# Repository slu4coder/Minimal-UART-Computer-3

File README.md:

# Minimal UART Computer 3 - Blinkenlights!

Here comes a big update of my DIY 'Minimal UART Computer', a machine built around a serial interface just from a handful of logic ICs, RAM and FLASH memory. For it's size, simplicity and self-imposed limitations, it's got double the processing power of a Commodore C64 or Apple II. It's mission is to be a fun learning platform for understanding computers on a fundamental level.

This is a free and non-commercial project. I am in no way associated with any activies selling the 'Minimal UART Computer' as a product. Any such activity represents a license violation. Individual licenses apply for hardware and software parts. Please refer to the applicable documentations for detailed licensing information. 

● Manual: https://docs.google.com/document/d/1nIM-WRrVe7SzYY-DS1jcVHC4TCuIhlQ6LCHnZnEml7k/edit?usp=sharing

● The Minimal UART Computer has a dedicated hardware serial 'Minimal Terminal': https://github.com/slu4coder/Minimal-Terminal
but can also be operated via a USB-to-serial breakout board and a terminal emulation (e. g. Tera Term) of cause.
  
OVERVIEW:

● Textbook 'Von-Neumann' architecture, 8-bit data bus, 16-bit address bus

● 64 instructions (conditional branching, subroutines, stack and word operations)

● 32KB RAM, 32KB SSD with file system (format, load, save, dir, delete, defrag, ...)

● Adjustable UART I/O (7 data bits, 2 stop bits, 9600bps – 500000bps)

● Adjustable CPU clock speed (single step – 8MHz)

● Processing power ~1.1Mips @ 8MHz comparable to 2x Commodore 64 or 2x Apple II

● Clear(est?) and simple(st? – you judge!) design

● ALU with 2 data registers A & B

● 3 flags (zero, negative, carry)

● 24 control signals

● Only 30(!) 74HCxx logic ICs, RAM and FLASH (an ATmega328p is used as a variable clock generator)

● NEW: Blinkenlights ;-)

● Operating system wiht native assembler and editor

● Games and demos (Tetris, Mandelbrot)

● Cycle-exact emulator, cross-assembler (Win64 and Linux)

I hope you find this information useful, educational or otherwise interesting. I'd love to hear about your build, so meet me on YouTube:

https://www.youtube.com/watch?v=wpls_rTcvJ8

https://www.youtube.com/channel/UCXYQcMpUBT3aaQKfmAVJNow

This is a free and non-commercial project. I am in no way associated with any activies selling this as a product.
Any such activity represents a license violation. Individual licenses apply for hardware and software parts. Please refer to the
appropriate documentations for detailed licensing information.

See https://github.com/slu4coder/Minimal-64x4-Home-Computer for a more feature-rich alternative with bitmap graphics, VGA and PS/2.

If you like this project and want to give something back, you can do so via PayPal. Thanks!

https://paypal.me/CarstenHerting

Have fun!

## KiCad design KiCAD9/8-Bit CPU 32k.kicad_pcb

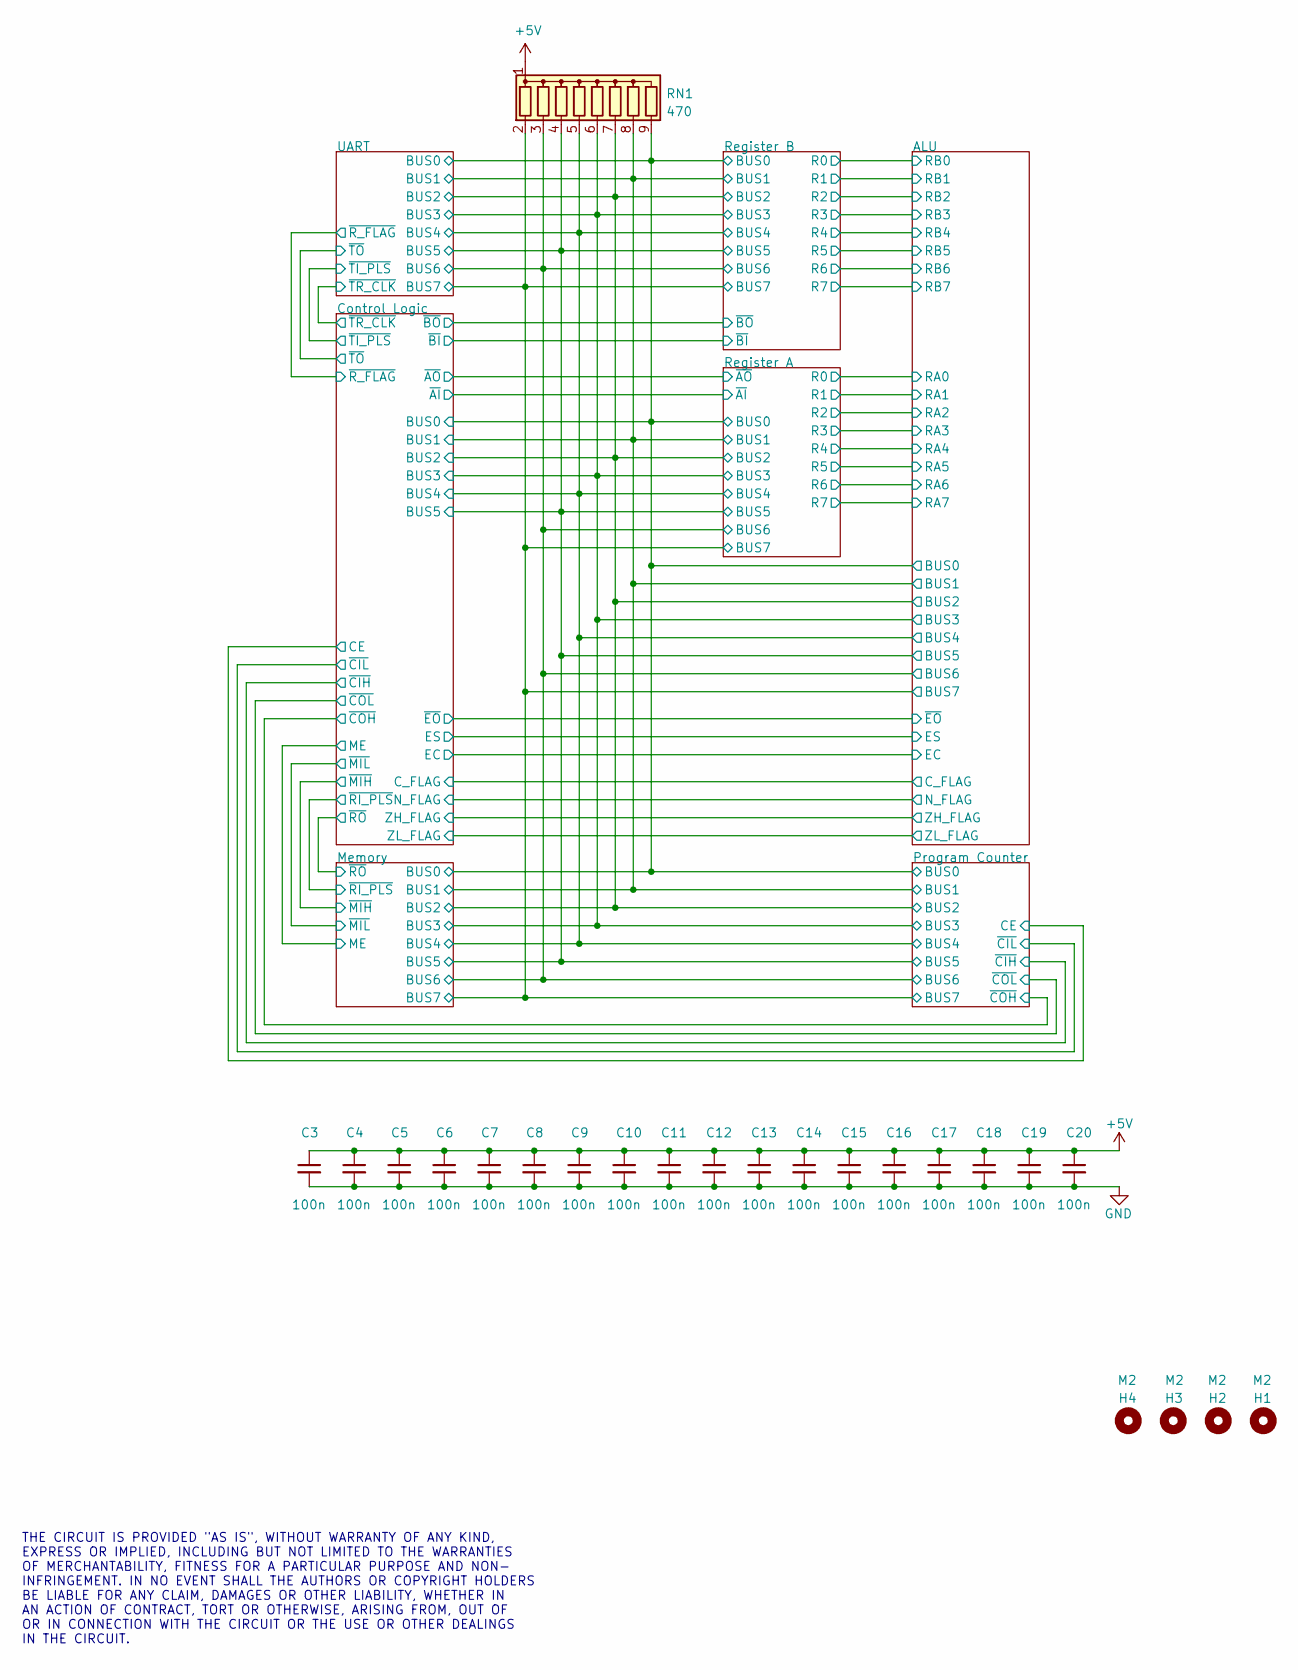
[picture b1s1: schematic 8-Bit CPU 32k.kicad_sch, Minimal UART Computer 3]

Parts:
C3, C4, C5, C6, C7, C8, C9, C10, C11, C12, C13, C14, C15, C16, C17, C18, C19, C20: 100n; C_Disc_D3.0mm_W2.0mm_P2.50mm
H1, H2, H3, H4: M2; MountingHole_2.2mm_M2
RN1: 470; R_Array_SIP9

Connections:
+5V: C3.1, C4.1, C5.1, C6.1, C7.1, C8.1, C9.1, C10.1, C11.1, C12.1, C13.1, C14.1, C15.1, C16.1, C17.1, C18.1, C19.1, C20.1, RN1.1 (common); also elsewhere on the board
/ALU/BUS0: RN1.9 (R8); also elsewhere on the board
/ALU/BUS1: RN1.8 (R7); also elsewhere on the board
/ALU/BUS2: RN1.7 (R6); also elsewhere on the board
/ALU/BUS3: RN1.6 (R5); also elsewhere on the board
/ALU/BUS4: RN1.5 (R4); also elsewhere on the board
/ALU/BUS5: RN1.4 (R3); also elsewhere on the board
/ALU/BUS6: RN1.3 (R2); also elsewhere on the board
/ALU/BUS7: RN1.2 (R1); also elsewhere on the board
GND: C3.2, C4.2, C5.2, C6.2, C7.2, C8.2, C9.2, C10.2, C11.2, C12.2, C13.2, C14.2, C15.2, C16.2, C17.2, C18.2, C19.2, C20.2; also elsewhere on the board

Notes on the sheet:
THE CIRCUIT IS PROVIDED "AS IS", WITHOUT WARRANTY OF ANY KIND, EXPRESS OR IMPLIED, INCLUDING BUT NOT LIMITED TO THE WARRANTIES OF MERCHANTABILITY, FITNESS FOR A PARTICULAR PURPOSE AND NON- INFRINGEMENT. IN NO EVENT SHALL THE AUTHORS OR COPYRIGHT HOLDERS BE LIABLE FOR ANY CLAIM, DAMAGES OR OTHER LIA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

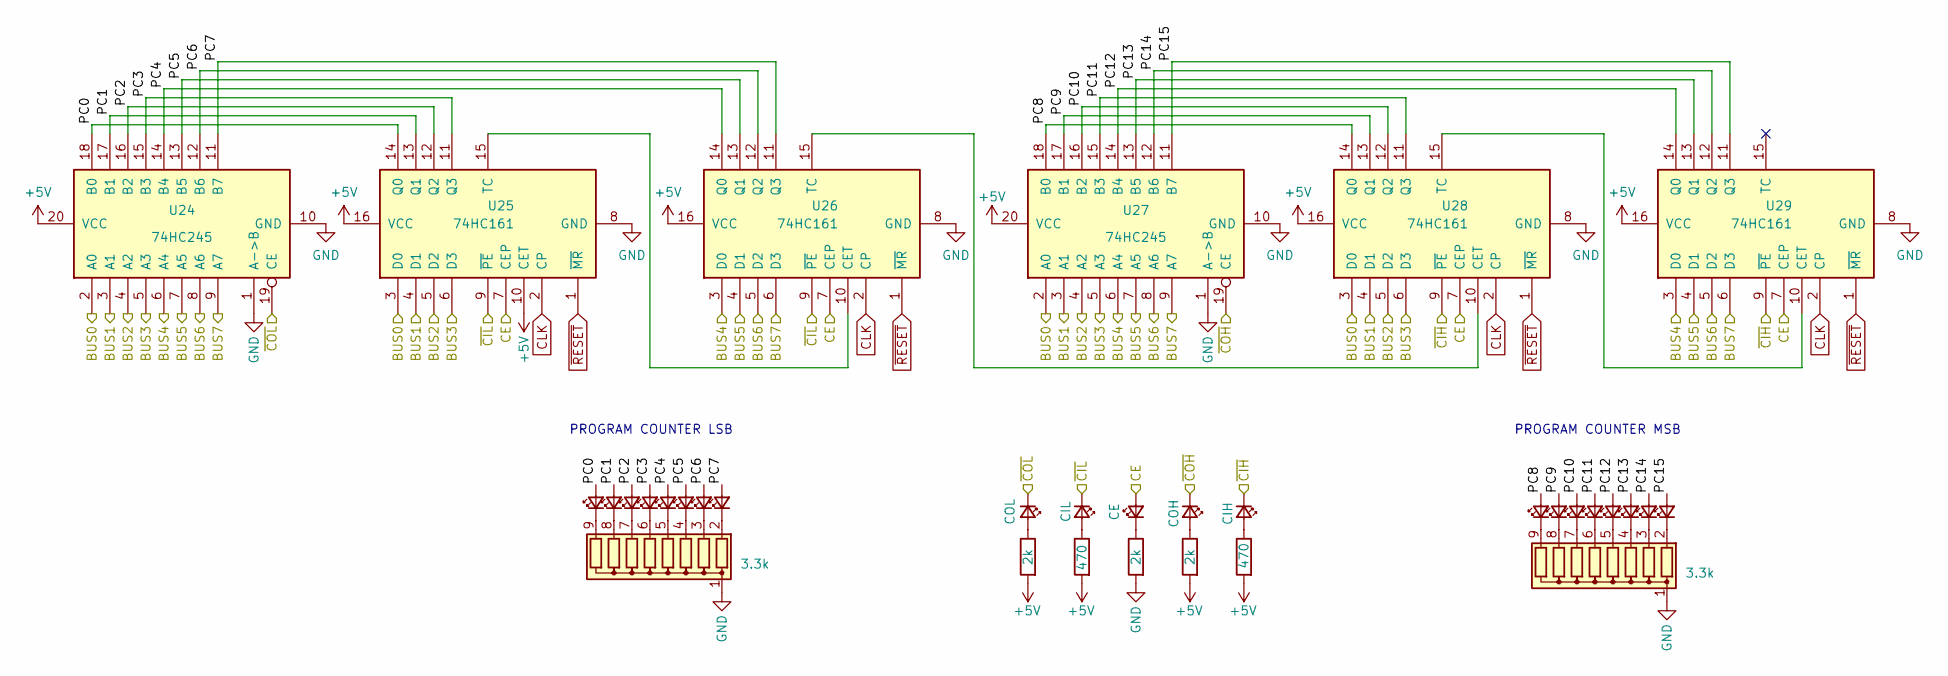
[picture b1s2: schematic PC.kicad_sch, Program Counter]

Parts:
D20, D21, D22, D23, D24, D25, D26, D27, D28, D29, D30, D31, D32, D33, D34, D35: LED_Small; LED_D5.0mm
D79: CIH; LED_D5.0mm
D81: COH; LED_D5.0mm
D83: COL; LED_D5.0mm
D84: CIL; LED_D5.0mm
D92: CE; LED_D5.0mm
R12, R17: 470; R_Axial_DIN0207_L6.3mm_D2.5mm_P7.62mm_Horizontal
R14, R16, R25: 2k; R_Axial_DIN0207_L6.3mm_D2.5mm_P7.62mm_Horizontal
RN4, RN5: 3.3k; R_Array_SIP9
U24, U27: 74HC245; DIP-20_W7.62mm
U25, U26, U28, U29: 74HC161; DIP-16_W7.62mm

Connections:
+5V: R12.2, R14.2, R16.2, R17.2, U24.20 (VCC), U25.10 (CET), U25.16 (VCC), U26.16 (VCC), U27.20 (VCC), U28.16 (VCC), U29.16 (VCC); also elsewhere on the board
/ALU/BUS0: U24.2 (A0), U25.3 (D0), U27.2 (A0), U28.3 (D0); also elsewhere on the board
/ALU/BUS1: U24.3 (A1), U25.4 (D1), U27.3 (A1), U28.4 (D1); also elsewhere on the board
/ALU/BUS2: U24.4 (A2), U25.5 (D2), U27.4 (A2), U28.5 (D2); also elsewhere on the board
/ALU/BUS3: U24.5 (A3), U25.6 (D3), U27.5 (A3), U28.6 (D3); also elsewhere on the board
/ALU/BUS4: U24.6 (A4), U26.3 (D0), U27.6 (A4), U29.3 (D0); also elsewhere on the board
/ALU/BUS5: U24.7 (A5), U26.4 (D1), U27.7 (A5), U29.4 (D1); also elsewhere on the board
/ALU/BUS6: U24.8 (A6), U26.5 (D2), U27.8 (A6), U29.5 (D2); also elsewhere on the board
/ALU/BUS7: U24.9 (A7), U26.6 (D3), U27.9 (A7), U29.6 (D3); also elsewhere on the board
/Control Logic/CE: D92.2 (A), U25.7 (CEP), U26.7 (CEP), U28.7 (CEP), U29.7 (CEP); also elsewhere on the board
/Control Logic/~CIH: D79.1 (K), U28.9 (~PE), U29.9 (~PE); also elsewhere on the board
/Control Logic/~CIL: D84.1 (K), U25.9 (~PE), U26.9 (~PE); also elsewhere on the board
/Control Logic/~COH: D81.1 (K), U27.19 (CE); also elsewhere on the board
/Control Logic/~COL: D83.1 (K), U24.19 (CE); also elsewhere on the board
/Program Counter/PC0: D20.2 (A), U24.18 (B0), U25.14 (Q0)
/Program Counter/PC1: D21.2 (A), U24.17 (B1), U25.13 (Q1)
/Program Counter/PC2: D22.2 (A), U24.16 (B2), U25.12 (Q2)
/Program Counter/PC3: D23.2 (A), U24.15 (B3), U25.11 (Q3)
/Program Counter/PC4: D24.2 (A), U24.14 (B4), U26.14 (Q0)
/Program Counter/PC5: D25.2 (A), U24.13 (B5), U26.13 (Q1)
/Program Counter/PC6: D26.2 (A), U24.12 (B6), U26.12 (Q2)
/Program Counter/PC7: D27.2 (A), U24.11 (B7), U26.11 (Q3)
/Program Counter/PC8: D28.2 (A), U27.18 (B0), U28.14 (Q0)
/Program Counter/PC9: D29.2 (A), U27.17 (B1), U28.13 (Q1)
/Program Counter/PC10: D30.2 (A), U27.16 (B2), U28.12 (Q2)
/Program Counter/PC11: D31.2 (A), U27.15 (B3), U28.11 (Q3)
/Program Counter/PC12: D32.2 (A), U27.14 (B4), U29.14 (Q0)
/Program Counter/PC13: D33.2 (A), U27.13 (B5), U29.13 (Q1)
/Program Counter/PC14: D34.2 (A), U27.12 (B6), U29.12 (Q2)
/Program Counter/PC15: D35.2 (A), U27.11 (B7), U29.11 (Q3)
CLK: U25.2 (CP), U26.2 (CP), U28.2 (CP), U29.2 (CP); also elsewhere on the board
GND: R25.2, RN4.1 (common), RN5.1 (common), U24.1 (A->B), U24.10 (GND), U25.8 (GND), U26.8 (GND), U27.1 (A->B), U27.10 (GND), U28.8 (GND), U29.8 (GND); also elsewhere on the board
unnamed: D20.1 (K), RN4.9 (R8)
unnamed: D21.1 (K), RN4.8 (R7)
unnamed: D22.1 (K), RN4.7 (R6)
unnamed: D23.1 (K), RN4.6 (R5)
unnamed: D24.1 (K), RN4.5 (R4)
unnamed: D25.1 (K), RN4.4 (R3)
unnamed: D26.1 (K), RN4.3 (R2)
unnamed: D27.1 (K), RN4.2 (R1)
unnamed: D28.1 (K), RN5.9 (R8)
unnamed: D29.1 (K), RN5.8 (R7)
unnamed: D30.1 (K), RN5.7 (R6)
unnamed: D31.1 (K), RN5.6 (R5)
unnamed: D32.1 (K), RN5.5 (R4)
unnamed: D33.1 (K), RN5.4 (R3)
unnamed: D34.1 (K), RN5.3 (R2)
unnamed: D35.1 (K), RN5.2 (R1)
unnamed: D79.2 (A), R12.1
unnamed: D81.2 (A), R14.1
unnamed: D83.2 (A), R16.1
unnamed: D84.2 (A), R17.1
unnamed: D92.1 (K), R25.1
unnamed: U25.15 (TC), U26.10 (CET)
unnamed: U26.15 (TC), U28.10 (CET)
unnamed: U28.15 (TC), U29.10 (CET)
~RESET: U25.1 (~MR), U26.1 (~MR), U28.1 (~MR), U29.1 (~MR); also elsewhere on the board

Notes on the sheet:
PROGRAM COUNTER MSB
PROGRAM COUNTER LSB

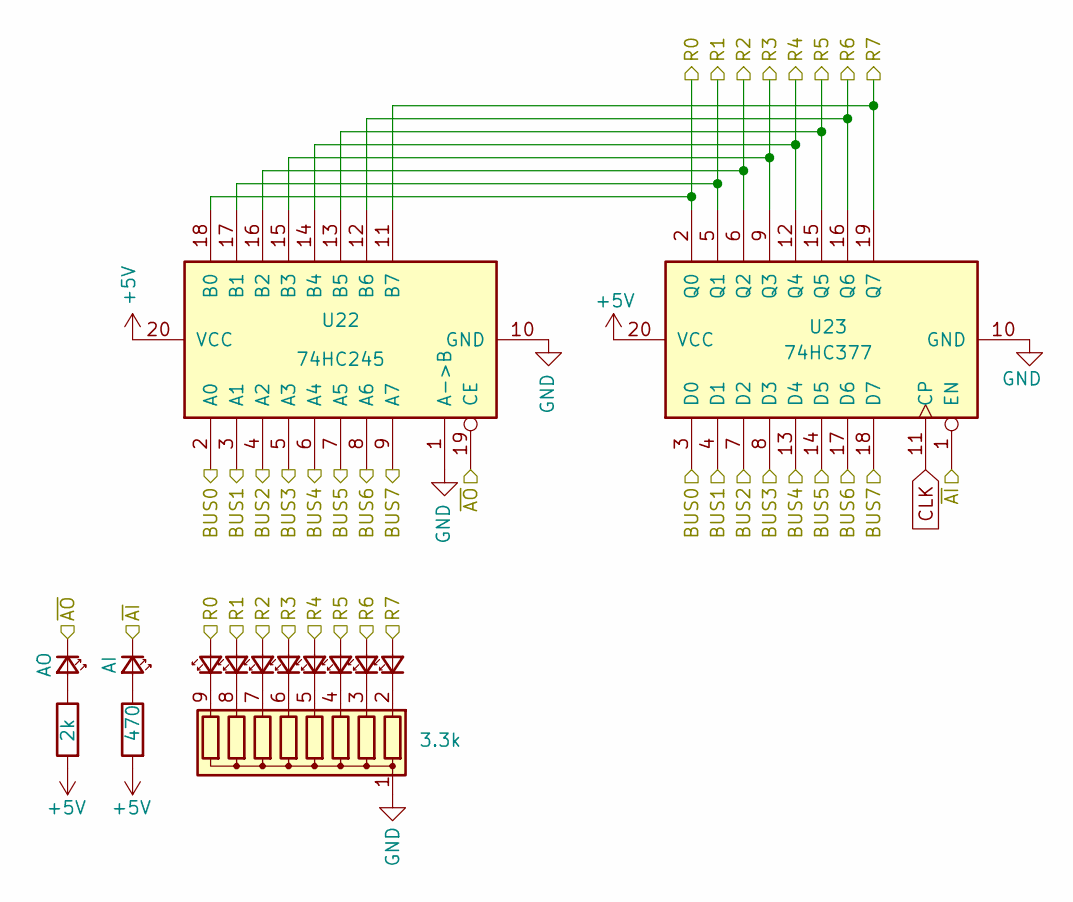
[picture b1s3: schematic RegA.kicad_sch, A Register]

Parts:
D36, D37, D38, D39, D40, D41, D42, D43: LED_Small; LED_D5.0mm
D65: AI; LED_D5.0mm
D66: AO; LED_D5.0mm
R7: 470; R_Axial_DIN0207_L6.3mm_D2.5mm_P7.62mm_Horizontal
R8: 2k; R_Axial_DIN0207_L6.3mm_D2.5mm_P7.62mm_Horizontal
RN6: 3.3k; R_Array_SIP9
U22: 74HC245; DIP-20_W7.62mm
U23: 74HC377; DIP-20_W7.62mm

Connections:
+5V: R7.2, R8.2, U22.20 (VCC), U23.20 (VCC); also elsewhere on the board
/ALU/BUS0: U22.2 (A0), U23.3 (D0); also elsewhere on the board
/ALU/BUS1: U22.3 (A1), U23.4 (D1); also elsewhere on the board
/ALU/BUS2: U22.4 (A2), U23.7 (D2); also elsewhere on the board
/ALU/BUS3: U22.5 (A3), U23.8 (D3); also elsewhere on the board
/ALU/BUS4: U22.6 (A4), U23.13 (D4); also elsewhere on the board
/ALU/BUS5: U22.7 (A5), U23.14 (D5); also elsewhere on the board
/ALU/BUS6: U22.8 (A6), U23.17 (D6); also elsewhere on the board
/ALU/BUS7: U22.9 (A7), U23.18 (D7); also elsewhere on the board
/ALU/RA0: D36.2 (A), U22.18 (B0), U23.2 (Q0); also elsewhere on the board
/ALU/RA1: D37.2 (A), U22.17 (B1), U23.5 (Q1); also elsewhere on the board
/ALU/RA2: D38.2 (A), U22.16 (B2), U23.6 (Q2); also elsewhere on the board
/ALU/RA3: D39.2 (A), U22.15 (B3), U23.9 (Q3); also elsewhere on the board
/ALU/RA4: D40.2 (A), U22.14 (B4), U23.12 (Q4); also elsewhere on the board
/ALU/RA5: D41.2 (A), U22.13 (B5), U23.15 (Q5); also elsewhere on the board
/ALU/RA6: D42.2 (A), U22.12 (B6), U23.16 (Q6); also elsewhere on the board
/ALU/RA7: D43.2 (A), U22.11 (B7), U23.19 (Q7); also elsewhere on the board
/Control Logic/~AI: D65.1 (K), U23.1 (EN); also elsewhere on the board
/Control Logic/~AO: D66.1 (K), U22.19 (CE); also elsewhere on the board
CLK: U23.11 (CP); also elsewhere on the board
GND: RN6.1 (common), U22.1 (A->B), U22.10 (GND), U23.10 (GND); also elsewhere on the board
unnamed: D36.1 (K), RN6.9 (R8)
unnamed: D37.1 (K), RN6.8 (R7)
unnamed: D38.1 (K), RN6.7 (R6)
unnamed: D39.1 (K), RN6.6 (R5)
unnamed: D40.1 (K), RN6.5 (R4)
unnamed: D41.1 (K), RN6.4 (R3)
unnamed: D42.1 (K), RN6.3 (R2)
unnamed: D43.1 (K), RN6.2 (R1)
unnamed: D65.2 (A), R7.1
unnamed: D66.2 (A), R8.1

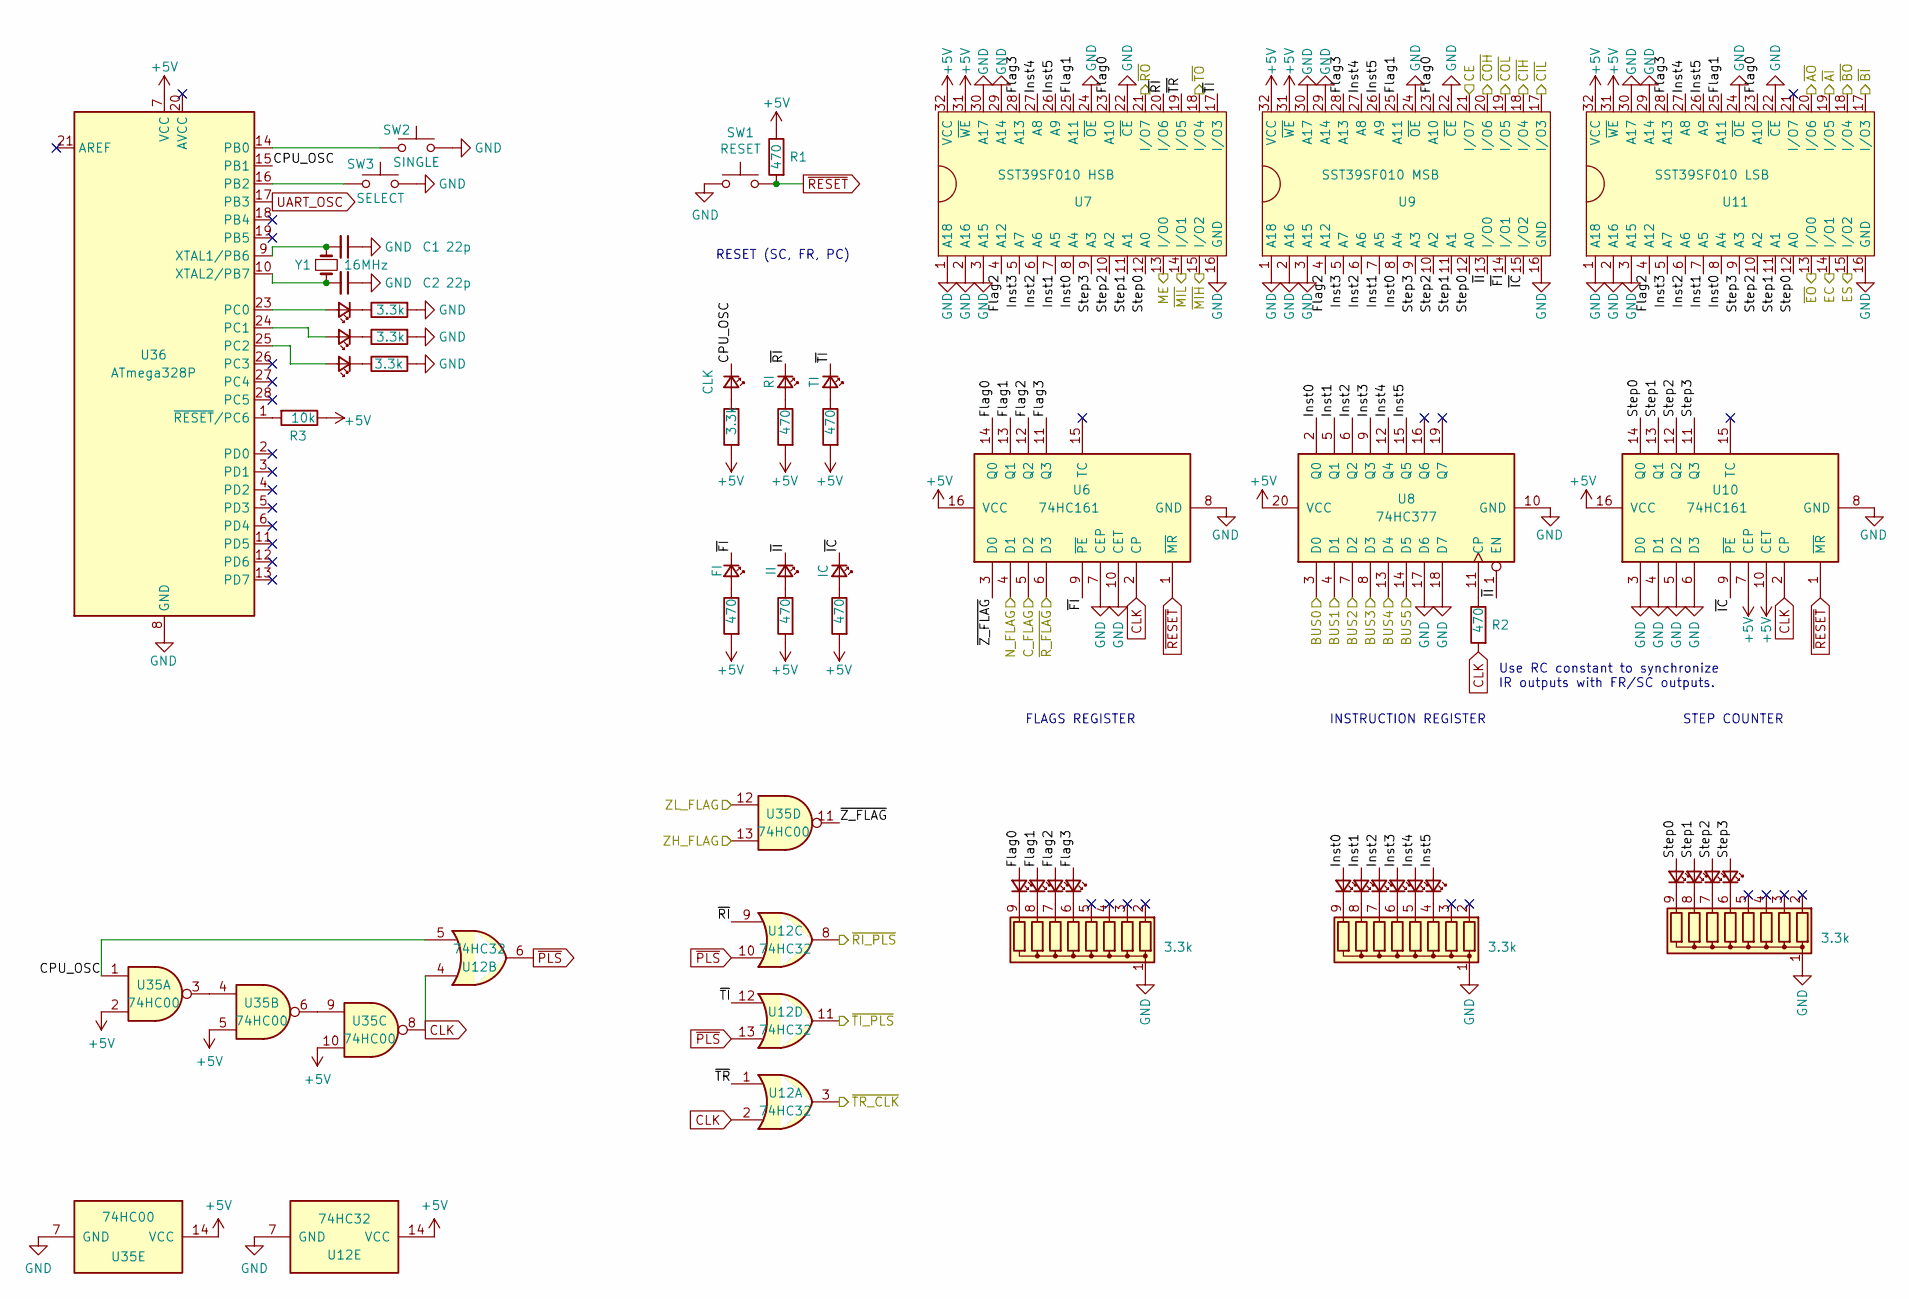
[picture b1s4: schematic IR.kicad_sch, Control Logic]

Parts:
C1, C2: 22p; C_Disc_D5.0mm_W2.5mm_P2.50mm
D1, D2, D3: LED_small; LED_D5.0mm
D60, D61, D62, D63, D64, D67, D68, D69, D70, D71, D72, D73, D74, D75: LED_Small; LED_D5.0mm
D82: RI; LED_D5.0mm
D87: TI; LED_D5.0mm
D89: FI; LED_D5.0mm
D90: II; LED_D5.0mm
D91: IC; LED_D5.0mm
D100: CLK; LED_D5.0mm
R1, R2, R15, R20, R22, R23, R24: 470; R_Axial_DIN0207_L6.3mm_D2.5mm_P7.62mm_Horizontal
R3: 10k; R_Axial_DIN0207_L6.3mm_D2.5mm_P7.62mm_Horizontal
R4, R5, R6, R33: 3.3k; R_Axial_DIN0207_L6.3mm_D2.5mm_P7.62mm_Horizontal
RN9, RN10, RN11: 3.3k; R_Array_SIP9
SW1: RESET; SW_PUSH_6mm
SW2: SINGLE; SW_PUSH_6mm
SW3: SELECT; SW_PUSH_6mm
U6, U10: 74HC161; DIP-16_W7.62mm
U7: SST39SF010 HSB; DIP-32_W15.24mm
U8: 74HC377; DIP-20_W7.62mm
U9: SST39SF010 MSB; DIP-32_W15.24mm
U11: SST39SF010 LSB; DIP-32_W15.24mm
U12: 74HC32; DIP-14_W7.62mm
U35: 74HC00; DIP-14_W7.62mm
U36: ATmega328P; DIP-28_W7.62mm
Y1: 16MHz; Crystal_HC18-U_Vertical

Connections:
+5V: R1.1, R3.1, R15.2, R20.2, R22.2, R23.2, R24.2, R33.2, U6.16 (VCC), U7.31 (~WE), U7.32 (VCC), U8.20 (VCC), U9.31 (~WE), U9.32 (VCC), U10.7 (CEP), U10.10 (CET), U10.16 (VCC), U11.31 (~WE), U11.32 (VCC), U12.14 (VCC), U35.2, U35.5, U35.10, U35.14 (VCC), U36.7 (VCC); also elsewhere on the board
/ALU/BUS0: U8.3 (D0); also elsewhere on the board
/ALU/BUS1: U8.4 (D1); also elsewhere on the board
/ALU/BUS2: U8.7 (D2); also elsewhere on the board
/ALU/BUS3: U8.8 (D3); also elsewhere on the board
/ALU/BUS4: U8.13 (D4); also elsewhere on the board
/ALU/BUS5: U8.14 (D5); also elsewhere on the board
/ALU/C_FLAG: U6.5 (D2); also elsewhere on the board
/ALU/EC: U11.14 (I/O1); also elsewhere on the board
/ALU/ES: U11.15 (I/O2); also elsewhere on the board
/ALU/N_FLAG: U6.4 (D1); also elsewhere on the board
/ALU/ZH_FLAG: U35.13; also elsewhere on the board
/ALU/ZL_FLAG: U35.12; also elsewhere on the board
/ALU/~EO: U11.13 (I/O0); also elsewhere on the board
/Control Logic/CE: U9.21 (I/O7); also elsewhere on the board
/Control Logic/CPU_OSC: D100.1 (K), U12.5, U35.1, U36.15 (PB1)
/Control Logic/Flag0: D71.2 (A), U6.14 (Q0), U7.23 (A10), U9.23 (A10), U11.23 (A10)
/Control Logic/Flag1: D70.2 (A), U6.13 (Q1), U7.25 (A11), U9.25 (A11), U11.25 (A11)
/Control Logic/Flag2: D69.2 (A), U6.12 (Q2), U7.4 (A12), U9.4 (A12), U11.4 (A12)
/Control Logic/Flag3: D68.2 (A), U6.11 (Q3), U7.28 (A13), U9.28 (A13), U11.28 (A13)
/Control Logic/Inst0: D63.2 (A), U7.8 (A4), U8.2 (Q0), U9.8 (A4), U11.8 (A4)
/Control Logic/Inst1: D62.2 (A), U7.7 (A5), U8.5 (Q1), U9.7 (A5), U11.7 (A5)
/Control Logic/Inst2: D61.2 (A), U7.6 (A6), U8.6 (Q2), U9.6 (A6), U11.6 (A6)
/Control Logic/Inst3: D60.2 (A), U7.5 (A7), U8.9 (Q3), U9.5 (A7), U11.5 (A7)
/Control Logic/Inst4: D64.2 (A), U7.27 (A8), U8.12 (Q4), U9.27 (A8), U11.27 (A8)
/Control Logic/Inst5: D67.2 (A), U7.26 (A9), U8.15 (Q5), U9.26 (A9), U11.26 (A9)
/Control Logic/ME: U7.13 (I/O0); also elsewhere on the board
/Control Logic/Step0: D75.2 (A), U7.12 (A0), U9.12 (A0), U10.14 (Q0), U11.12 (A0)
/Control Logic/Step1: D74.2 (A), U7.11 (A1), U9.11 (A1), U10.13 (Q1), U11.11 (A1)
/Control Logic/Step2: D73.2 (A), U7.10 (A2), U9.10 (A2), U10.12 (Q2), U11.10 (A2)
/Control Logic/Step3: D72.2 (A), U7.9 (A3), U9.9 (A3), U10.11 (Q3), U11.9 (A3)
/Control Logic/~AI: U11.19 (I/O5); also elsewhere on the board
/Control Logic/~AO: U11.20 (I/O6); also elsewhere on the board
/Control Logic/~BI: U11.17 (I/O3); also elsewhere on the board
/Control Logic/~BO: U11.18 (I/O4); also elsewhere on the board
/Control Logic/~CIH: U9.18 (I/O4); also elsewhere on the board
/Control Logic/~CIL: U9.17 (I/O3); also elsewhere on the board
/Control Logic/~COH: U9.20 (I/O6); also elsewhere on the board
/Control Logic/~COL: U9.19 (I/O5); also elsewhere on the board
/Control Logic/~FI: D89.1 (K), U6.9 (~PE), U9.14 (I/O1)
/Control Logic/~IC: D91.1 (K), U9.15 (I/O2), U10.9 (~PE)
/Control Logic/~II: D90.1 (K), U8.1 (EN), U9.13 (I/O0)
/Control Logic/~MIH: U7.15 (I/O2); also elsewhere on the board
/Control Logic/~MIL: U7.14 (I/O1); also elsewhere on the board
/Control Logic/~RI_PLS: U12.8; also elsewhere on the board
/Control Logic/~RI: D82.1 (K), U7.20 (I/O6), U12.9
/Control Logic/~RO: U7.21 (I/O7); also elsewhere on the board
/Control Logic/~R_FLAG: U6.6 (D3); also elsewhere on the board
/Control Logic/~TI_PLS: U12.11; also elsewhere on the board
/Control Logic/~TI: D87.1 (K), U7.17 (I/O3), U12.12
/Control Logic/~TO: U7.18 (I/O4); also elsewhere on the board
/Control Logic/~TR_PLS: U12.3; also elsewhere on the board
/Control Logic/~TR: U7.19 (I/O5), U12.1
/Control Logic/~Z_FLAG: U6.3 (D0), U35.11
CLK: R2.2, U6.2 (CP), U10.2 (CP), U12.2, U12.4, U35.8; also elsewhere on the board
GND: C1.1, C2.1, R4.2, R5.2, R6.2, RN9.1 (common), RN10.1 (common), RN11.1 (common), SW1.2, SW2.1, SW3.1, U6.7 (CEP), U6.8 (GND), U6.10 (CET), U7.1 (A18), U7.2 (A16), U7.3 (A15), U7.16 (GND), U7.22 (~CE), U7.24 (~OE), U7.29 (A14), U7.30 (A17), U8.10 (GND), U8.17 (D6), U8.18 (D7), U9.1 (A18), U9.2 (A16), U9.3 (A15), U9.16 (GND), U9.22 (~CE), U9.24 (~OE), U9.29 (A14), U9.30 (A17), U10.3 (D0), U10.4 (D1), U10.5 (D2), U10.6 (D3), U10.8 (GND), U11.1 (A18), U11.2 (A16), U11.3 (A15), U11.16 (GND), U11.22 (~CE), U11.24 (~OE), U11.29 (A14), U11.30 (A17), U12.7 (GND), U35.7 (GND), U36.8 (GND), U36.22 (GND); also elsewhere on the board
unnamed: D1.2 (A), U36.25 (PC2)
unnamed: D1.1 (K), R4.1
unnamed: D2.2 (A), U36.24 (PC1)
unnamed: D2.1 (K), R5.1
unnamed: D3.2 (A), U36.23 (PC0)
unnamed: D3.1 (K), R6.1
unnamed: D60.1 (K), RN9.6 (R5)
unnamed: D61.1 (K), RN9.7 (R6)
unnamed: D62.1 (K), RN9.8 (R7)
unnamed: D63.1 (K), RN9.9 (R8)
unnamed: D64.1 (K), RN9.5 (R4)
unnamed: D67.1 (K), RN9.4 (R3)
unnamed: D68.1 (K), RN11.6 (R5)
unnamed: D69.1 (K), RN11.7 (R6)
unnamed: D70.1 (K), RN11.8 (R7)
unnamed: D71.1 (K), RN11.9 (R8)
unnamed: D72.1 (K), RN10.6 (R5)
unnamed: D73.1 (K), RN10.7 (R6)
unnamed: D74.1 (K), RN10.8 (R7)
unnamed: D75.1 (K), RN10.9 (R8)
unnamed: D82.2 (A), R15.1
unnamed: D87.2 (A), R20.1
unnamed: D89.2 (A), R22.1
unnamed: D90.2 (A), R23.1
unnamed: D91.2 (A), R24.1
unnamed: D100.2 (A), R33.1
unnamed: R2.1, U8.11 (CP)
unnamed: U35.3, U35.4
unnamed: U35.6, U35.9
unnamed: SW2.2, U36.14 (PB0)
unnamed: SW3.2, U36.16 (PB2)
unnamed: C1.2, U36.9 (XTAL1/PB6), Y1.1
unnamed: C2.2, U36.10 (XTAL2/PB7), Y1.2
unnamed: R3.2, U36.1 (~RESET/PC6)
UART_OSC: U36.17 (PB3); also elsewhere on the board
~PLS: U12.6, U12.10, U12.13; also elsewhere on the board
~RESET: R1.2, SW1.1, U6.1 (~MR), U10.1 (~MR); also elsewhere on the board

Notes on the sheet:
INSTRUCTION REGISTER
RESET (SC, FR, PC)
STEP COUNTER
FLAGS REGISTER
Use RC constant to synchronize IR outputs with FR/SC outputs.

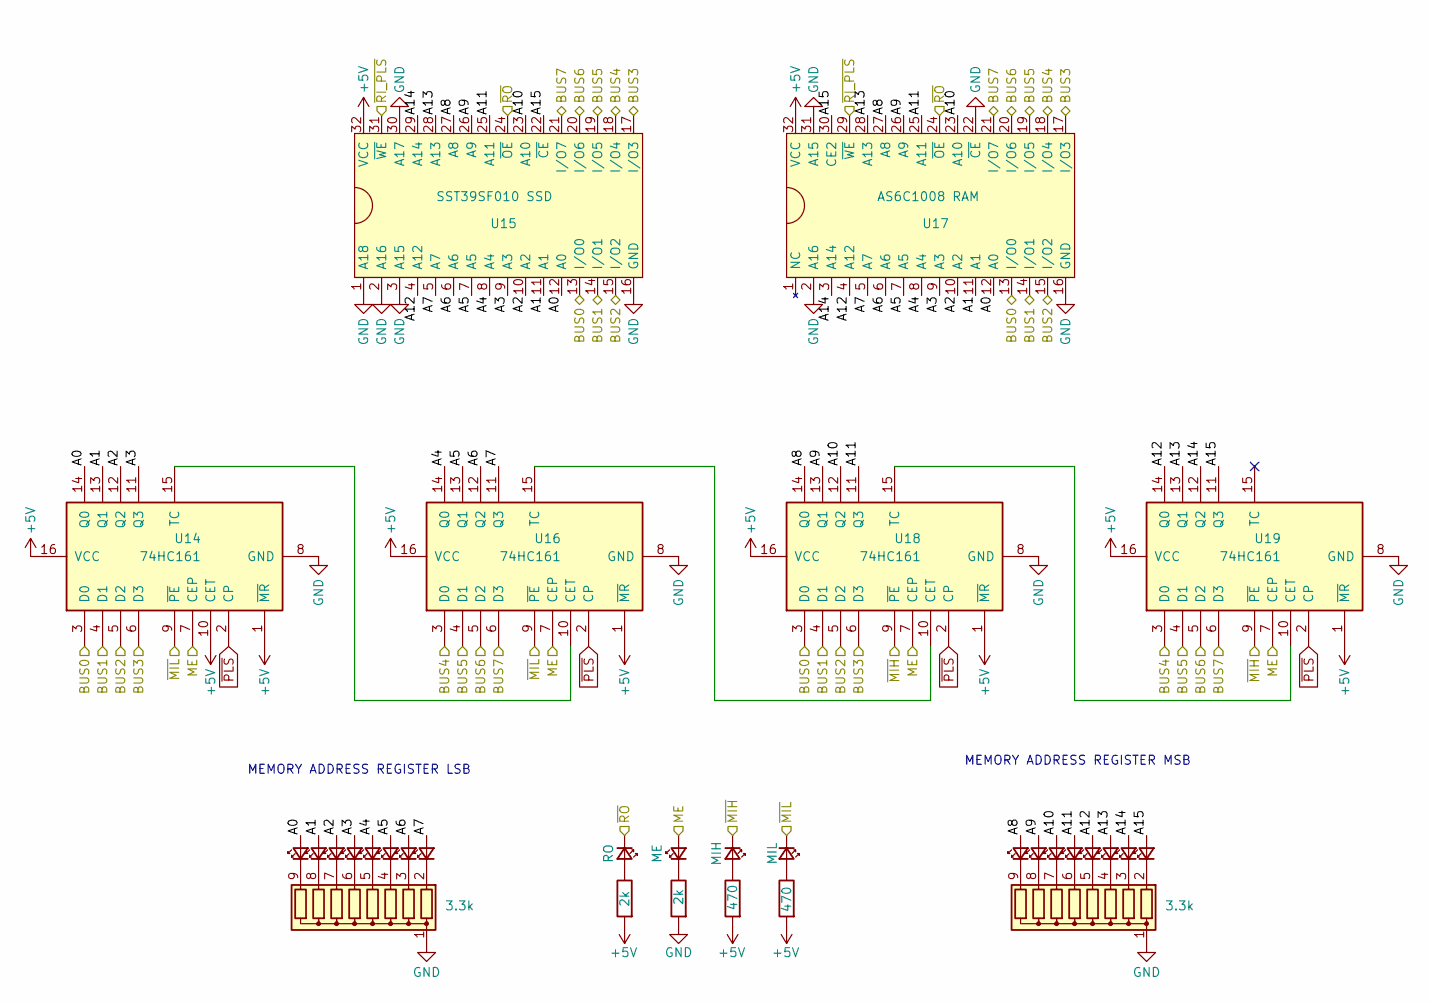
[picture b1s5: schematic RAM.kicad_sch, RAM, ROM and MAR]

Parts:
D4, D5, D6, D7, D8, D9, D10, D11, D12, D13, D14, D15, D16, D17, D18, D19: LED_Small; LED_D5.0mm
D85: MIL; LED_D5.0mm
D86: MIH; LED_D5.0mm
D88: ME; LED_D5.0mm
D99: RO; LED_D5.0mm
R18, R19: 470; R_Axial_DIN0207_L6.3mm_D2.5mm_P7.62mm_Horizontal
R21, R32: 2k; R_Axial_DIN0207_L6.3mm_D2.5mm_P7.62mm_Horizontal
RN2, RN3: 3.3k; R_Array_SIP9
U14, U16, U18, U19: 74HC161; DIP-16_W7.62mm
U15: SST39SF010 SSD; DIP-32_W15.24mm
U17: AS6C1008 RAM; DIP-32_W15.24mm

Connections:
+5V: R18.2, R19.2, R32.2, U14.1 (~MR), U14.10 (CET), U14.16 (VCC), U15.32 (VCC), U16.1 (~MR), U16.16 (VCC), U17.32 (VCC), U18.1 (~MR), U18.16 (VCC), U19.1 (~MR), U19.16 (VCC); also elsewhere on the board
/ALU/BUS0: U14.3 (D0), U15.13 (I/O0), U17.13 (I/O0), U18.3 (D0); also elsewhere on the board
/ALU/BUS1: U14.4 (D1), U15.14 (I/O1), U17.14 (I/O1), U18.4 (D1); also elsewhere on the board
/ALU/BUS2: U14.5 (D2), U15.15 (I/O2), U17.15 (I/O2), U18.5 (D2); also elsewhere on the board
/ALU/BUS3: U14.6 (D3), U15.17 (I/O3), U17.17 (I/O3), U18.6 (D3); also elsewhere on the board
/ALU/BUS4: U15.18 (I/O4), U16.3 (D0), U17.18 (I/O4), U19.3 (D0); also elsewhere on the board
/ALU/BUS5: U15.19 (I/O5), U16.4 (D1), U17.19 (I/O5), U19.4 (D1); also elsewhere on the board
/ALU/BUS6: U15.20 (I/O6), U16.5 (D2), U17.20 (I/O6), U19.5 (D2); also elsewhere on the board
/ALU/BUS7: U15.21 (I/O7), U16.6 (D3), U17.21 (I/O7), U19.6 (D3); also elsewhere on the board
/Control Logic/ME: D88.2 (A), U14.7 (CEP), U16.7 (CEP), U18.7 (CEP), U19.7 (CEP); also elsewhere on the board
/Control Logic/~MIH: D86.1 (K), U18.9 (~PE), U19.9 (~PE); also elsewhere on the board
/Control Logic/~MIL: D85.1 (K), U14.9 (~PE), U16.9 (~PE); also elsewhere on the board
/Control Logic/~RI_PLS: U15.31 (~WE), U17.29 (~WE); also elsewhere on the board
/Control Logic/~RO: D99.1 (K), U15.24 (~OE), U17.24 (~OE); also elsewhere on the board
/Memory/A0: D7.2 (A), U14.14 (Q0), U15.12 (A0), U17.12 (A0)
/Memory/A1: D6.2 (A), U14.13 (Q1), U15.11 (A1), U17.11 (A1)
/Memory/A2: D5.2 (A), U14.12 (Q2), U15.10 (A2), U17.10 (A2)
/Memory/A3: D4.2 (A), U14.11 (Q3), U15.9 (A3), U17.9 (A3)
/Memory/A4: D11.2 (A), U15.8 (A4), U16.14 (Q0), U17.8 (A4)
/Memory/A5: D10.2 (A), U15.7 (A5), U16.13 (Q1), U17.7 (A5)
/Memory/A6: D9.2 (A), U15.6 (A6), U16.12 (Q2), U17.6 (A6)
/Memory/A7: D8.2 (A), U15.5 (A7), U16.11 (Q3), U17.5 (A7)
/Memory/A8: D12.2 (A), U15.27 (A8), U17.27 (A8), U18.14 (Q0)
/Memory/A9: D13.2 (A), U15.26 (A9), U17.26 (A9), U18.13 (Q1)
/Memory/A10: D14.2 (A), U15.23 (A10), U17.23 (A10), U18.12 (Q2)
/Memory/A11: D15.2 (A), U15.25 (A11), U17.25 (A11), U18.11 (Q3)
/Memory/A12: D16.2 (A), U15.4 (A12), U17.4 (A12), U19.14 (Q0)
/Memory/A13: D17.2 (A), U15.28 (A13), U17.28 (A13), U19.13 (Q1)
/Memory/A14: D18.2 (A), U15.29 (A14), U17.3 (A14), U19.12 (Q2)
/Memory/A15: D19.2 (A), U15.22 (~CE), U17.30 (CE2), U19.11 (Q3)
GND: R21.2, RN2.1 (common), RN3.1 (common), U14.8 (GND), U15.1 (A18), U15.2 (A16), U15.3 (A15), U15.16 (GND), U15.30 (A17), U16.8 (GND), U17.2 (A16), U17.16 (GND), U17.22 (~CE), U17.31 (A15), U18.8 (GND), U19.8 (GND); also elsewhere on the board
unnamed: D4.1 (K), RN2.6 (R5)
unnamed: D5.1 (K), RN2.7 (R6)
unnamed: D6.1 (K), RN2.8 (R7)
unnamed: D7.1 (K), RN2.9 (R8)
unnamed: D8.1 (K), RN2.2 (R1)
unnamed: D9.1 (K), RN2.3 (R2)
unnamed: D10.1 (K), RN2.4 (R3)
unnamed: D11.1 (K), RN2.5 (R4)
unnamed: D12.1 (K), RN3.9 (R8)
unnamed: D13.1 (K), RN3.8 (R7)
unnamed: D14.1 (K), RN3.7 (R6)
unnamed: D15.1 (K), RN3.6 (R5)
unnamed: D16.1 (K), RN3.5 (R4)
unnamed: D17.1 (K), RN3.4 (R3)
unnamed: D18.1 (K), RN3.3 (R2)
unnamed: D19.1 (K), RN3.2 (R1)
unnamed: D85.2 (A), R18.1
unnamed: D86.2 (A), R19.1
unnamed: D88.1 (K), R21.1
unnamed: D99.2 (A), R32.1
unnamed: U14.15 (TC), U16.10 (CET)
unnamed: U16.15 (TC), U18.10 (CET)
unnamed: U18.15 (TC), U19.10 (CET)
~PLS: U14.2 (CP), U16.2 (CP), U18.2 (CP), U19.2 (CP); also elsewhere on the board

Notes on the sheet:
MEMORY ADDRESS REGISTER LSB
MEMORY ADDRESS REGISTER MSB

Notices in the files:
KiCAD9/8-Bit CPU 32k.kicad_pcb:
Licensed under CC BY-NC-SA 4.0  http://creativecommons.org/licenses/by-nc-sa/4.0
KiCAD9/8-Bit CPU 32k.kicad_sch:
This work is licensed under CC BY-NC-SA 4.0
Support/Emulator/src/main.cpp:
This file is free software: you can redistribute it and/or modify it under the terms of the
GNU General Public License as published by the Free Software Foundation, either
